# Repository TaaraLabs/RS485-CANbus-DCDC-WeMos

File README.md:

RS485-CanBus-WeMos
==================

RS-485+CanBus+DCDC Converter Shield for WeMos D1 Mini32

[Official WebSite](https://taaralabs.eu/cw1)

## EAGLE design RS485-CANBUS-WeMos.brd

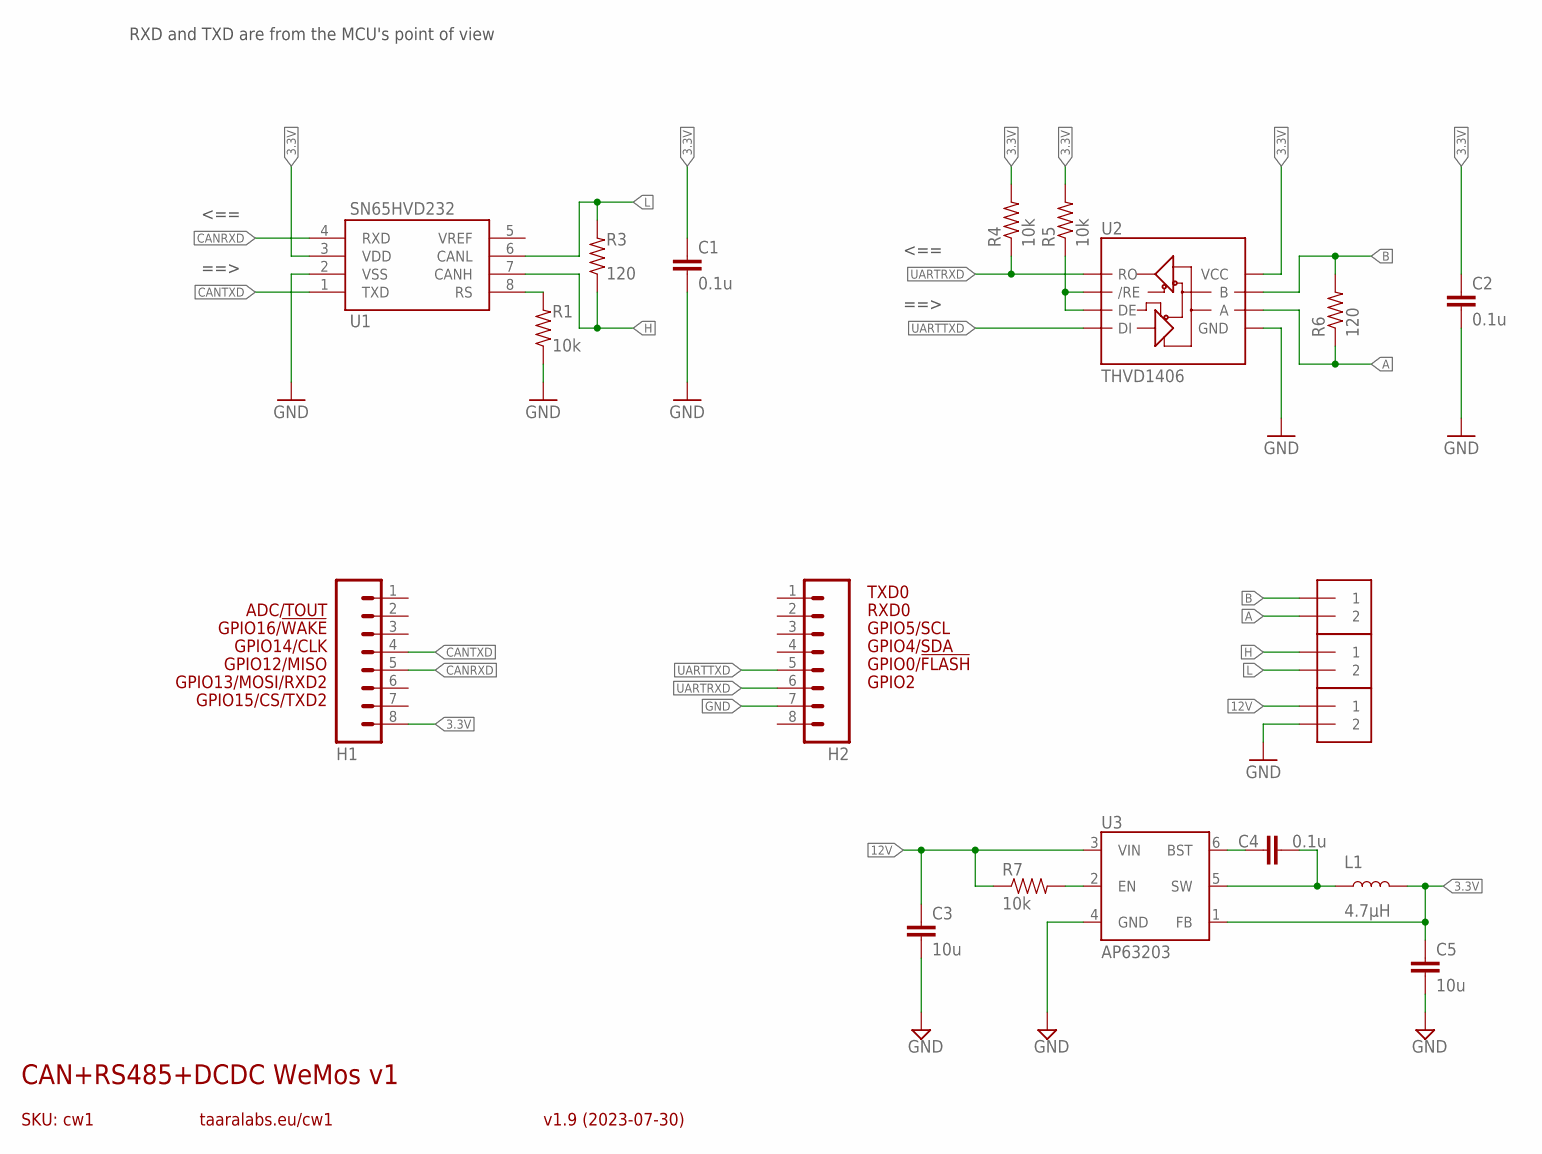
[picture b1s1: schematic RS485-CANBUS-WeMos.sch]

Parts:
C1, C2, C4: 0.1u; 0805
C3: 10u; 1210
C5: 10u; 0805
H1, H2: M08; 1X08
J1, J2, J3: 1X2-3.5MM
L1: 4.7μH; INDUCTOR_4X4MM
R1, R4, R5, R7: 10k; 0805
R3, R6: 120; 0805
U1: SN65HVD232; SO08
U2: THVD1406; SO08
U3: AP63203; SOT23-6

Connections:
3.3V: C1.1, C2.1, C5.1, H1.8, L1.P$2 (2), R4.2, R5.2, U1.3 (VDD), U2.8 (VCC), U3.1 (FB)
12V: C3.1, J2.1, R7.1, U3.3 (VIN)
/SHDN: R5.1, U2.2 (/RE), U2.3 (DE)
A: J3.2, R6.1, U2.6 (A)
B: J3.1, R6.2, U2.7 (B)
BST: C4.1, U3.6 (BST)
CANRXD: H1.5, U1.4 (RXD)
CANTXD: H1.4, U1.1 (TXD)
EN: R7.2, U3.2 (EN)
GND: C1.2, C2.2, C3.2, C5.2, H2.7, J2.2, R1.1, U1.2 (VSS), U2.5 (GND), U3.4 (GND)
H: J1.1, R3.1, U1.7 (CANH)
L: J1.2, R3.2, U1.6 (CANL)
RS: R1.2, U1.8 (RS)
SW: C4.2, L1.P$1 (1), U3.5 (SW)
UARTRXD: H2.6, R4.1, U2.1 (RO)
UARTTXD: H2.5, U2.4 (DI)

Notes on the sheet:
GPIO2
GPIO0/!FLASH
GPIO12/MISO
GPIO4/SDA
GPIO5/SCL
RXD0
TXD0
GPIO13/MOSI/RXD2
GPIO14/CLK
GPIO15/CS/TXD2
GPIO16/!WAKE
SKU: cw1
CAN+RS485+DCDC WeMos v1
v1.9 (2023-07-30)
taaralabs.eu/cw1
ADC/TOUT
<==
==>
RXD and TXD are from the MCU's point of view

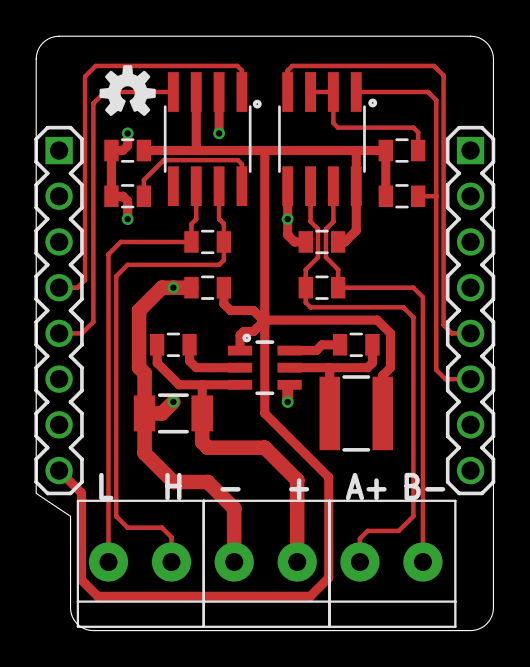
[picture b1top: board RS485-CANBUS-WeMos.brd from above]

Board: 2 copper layers, 25.4 x 33.0 mm, 22 parts (1 on the bottom side), 16 nets.

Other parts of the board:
U$1, U$2: OSHW-LOGO-S

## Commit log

2023-06-07 CAN Transceiver datasheet added
2023-07-31 New revision
2023-07-31 Datasheet for THVD1426 RS485 transceiver
2023-07-31 Datasheet for AP63203 DCDC converter chip
2023-07-31 cleanup
2023-07-31 WeMos ESP32 D1 Mini pinout
2025-03-12 Board definitions for ESP32-NMEA2000
2025-03-12 USBSerial added
2025-03-12 ESP32C3 not compiling
2025-03-13 CAN and RS485 Serial working on ESP32C3 without USB
2025-03-13 disclaimer about ESP32C3
2025-03-13 correction
2025-03-13 some pictures
2025-03-15 firmware binaries
2025-03-15 README added
2025-03-15 explanation of different firmwares added
2025-03-15 photos added

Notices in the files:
parts and their libraries:
freetronics-original: Licensing: CC v3.0 Share-Alike You are welcome to use this library for commercial purposes.
SparkFun-DigitalIC: Licensing: Creative Commons ShareAlike 4.0 International - https://creativecommons.org/licenses/by-sa/4.0
